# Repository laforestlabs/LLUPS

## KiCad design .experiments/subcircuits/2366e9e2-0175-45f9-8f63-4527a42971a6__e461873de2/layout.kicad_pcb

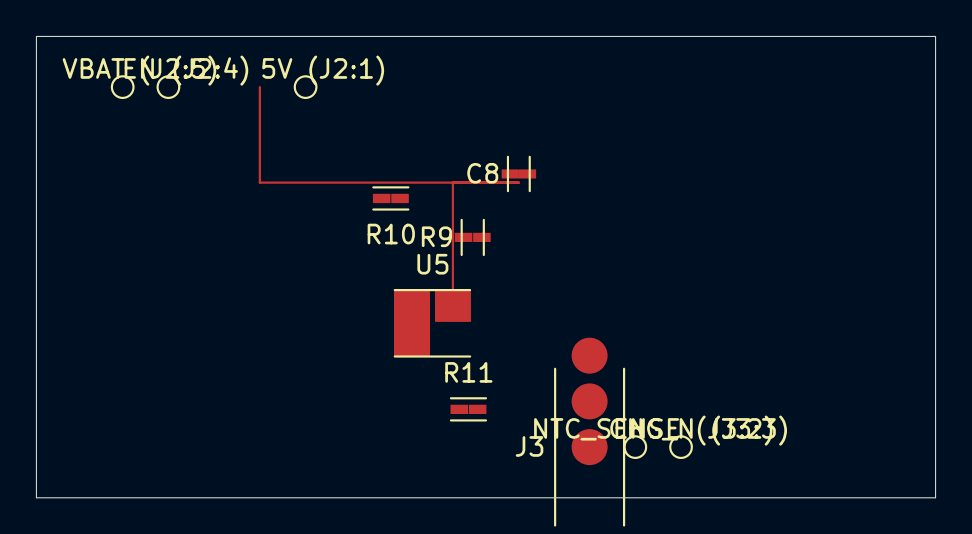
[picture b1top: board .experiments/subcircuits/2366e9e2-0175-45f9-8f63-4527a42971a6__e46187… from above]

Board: 2 copper layers, 50.0 x 25.6 mm, 7 parts (1 on the bottom side), 6 nets.

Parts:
C8: 1u
J2: Output
J3: Debug
R9: 75k
R10: 10k
R11: 100k
U5: AP2112K-3.3

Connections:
/3V3: C8.1, J2.2, U5.5
/5V: J2.1, R9.1, U5.1
/EN: J2.4, R11.2, U5.3
/VBAT: J2.5, J3.1
GND: C8.2, J2.3, R10.2, U5.2
unnamed: R9.2, R10.1

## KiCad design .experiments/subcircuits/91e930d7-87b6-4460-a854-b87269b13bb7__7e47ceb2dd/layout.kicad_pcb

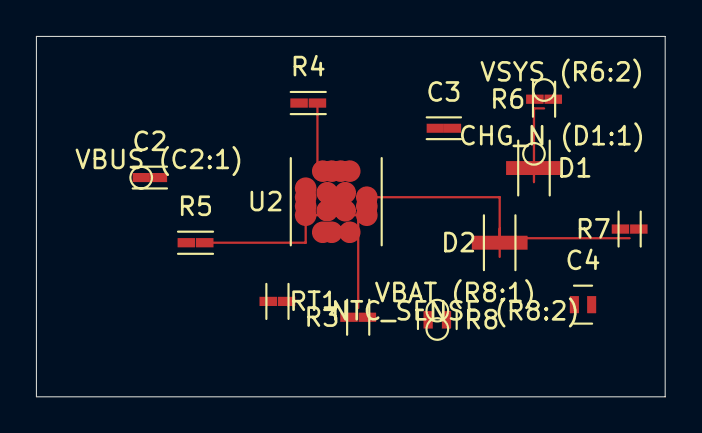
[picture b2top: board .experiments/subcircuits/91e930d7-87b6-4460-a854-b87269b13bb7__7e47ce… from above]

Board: 2 copper layers, 34.9 x 20.0 mm, 13 parts (0 on the bottom side), 12 nets.

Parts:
C2, C3, C4: 4.7u
D1: CHG
D2: PGOOD
R3, R6, R7: 1k
R4: 1.5k
R5, R8: 10k
RT1: 10k_NTC
U2: BQ24072

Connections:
/CHG_N: D1.1, U2.9
/NTC_SENSE: R8.2, RT1.1, U2.1
/VBAT: C4.1, R8.1, U2.2, U2.3
/VBUS: C2.1, U2.13
/VSYS: C3.1, R6.2, R7.2, U2.5, U2.6, U2.10, U2.11
GND: C2.2, C3.2, C4.2, R3.1, R4.1, R5.1, RT1.2, U2.8, U2.17
unnamed: D1.2, R6.1
unnamed: D2.2, R7.1
unnamed: D2.1, U2.7
unnamed: R4.2, U2.12
unnamed: R3.2, U2.16
unnamed: R5.2, U2.14

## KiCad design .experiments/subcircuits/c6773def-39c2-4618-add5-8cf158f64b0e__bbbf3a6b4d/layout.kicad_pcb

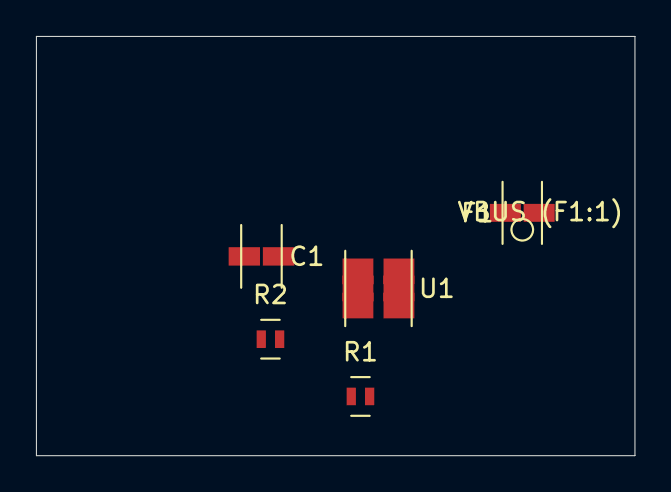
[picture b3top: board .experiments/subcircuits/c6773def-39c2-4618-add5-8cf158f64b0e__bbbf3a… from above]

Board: 2 copper layers, 33.2 x 23.3 mm, 6 parts (1 on the bottom side), 7 nets, no tracks yet.

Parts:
C1: 10u
F1: 2A_PTC
J1: USB_C
R1, R2: 5.1k
U1: USBLC6-2SC6

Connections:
/VBUS: C1.1, F1.1, U1.5
GND: C1.2, J1.A1, J1.A12, J1.B1, J1.B12, J1.S1, R1.2, R2.2, U1.2
unnamed: F1.2, J1.A4, J1.A9, J1.B4, J1.B9
unnamed: J1.A5, U1.1
unnamed: J1.B5, U1.3
unnamed: R1.1, U1.6
unnamed: R2.1, U1.4

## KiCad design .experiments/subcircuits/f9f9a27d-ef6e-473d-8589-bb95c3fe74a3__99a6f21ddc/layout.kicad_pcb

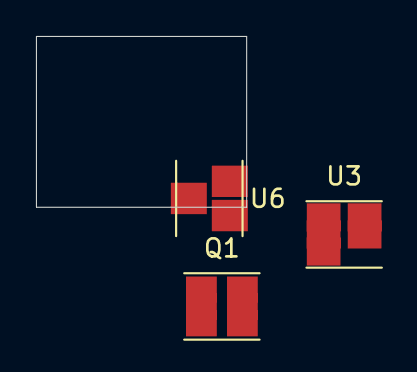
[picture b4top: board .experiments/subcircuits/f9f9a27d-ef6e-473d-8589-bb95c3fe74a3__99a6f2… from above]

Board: 2 copper layers, 11.7 x 9.5 mm, 3 parts (0 on the bottom side), 6 nets, no tracks yet.

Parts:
Q1: FS8205A
U3: HY2113-KB5B
U6: LN61CN3302MR-G

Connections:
/CELL_NEG: Q1.4, U3.6
/VBAT: U3.5, U6.1
GND: Q1.1, U3.2, U6.2
unnamed: Q1.3, Q1.6
unnamed: Q1.2, U3.1
unnamed: Q1.5, U3.3
